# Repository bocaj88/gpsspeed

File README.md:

# GPSSpeed: a GPS replacement for the PerfectPass paddlewheel

**A small board that reads GPS speed and feeds it to PerfectPass as if it were the paddlewheel.**
Built for, and being tested on, our **2008 MasterCraft X2**. Everything is open: schematic, PCB,
firmware, and the notes on what didn't work along the way.

## The problem

**The paddlewheel speed sensor on our X2 went bad, and replacement sensors aren't sold anymore.**
Without it, PerfectPass has no speed to hold, so the speed control on the boat was dead.

PerfectPass holds a tow boat at a set speed by reading the boat's **paddlewheel speed sensor**: a
small wheel under the hull that spins in the water and sends one pulse per fraction of a turn.
On our X2 that sensor is part of an Airmar DST800-style triducer (speed, depth, temperature). It
sends about 20,000 pulses per nautical mile, and PerfectPass turns the pulse rate into speed.

Paddlewheels are the weak link:

- **They foul.** Weed, a fishing line, or a little growth, and the wheel drags or stops. PerfectPass
  then sees the wrong speed (or none) and drives the throttle accordingly.
- **You can't buy a replacement.** The DST800 is now an Airmar *legacy* product. Ours failed, and
  there was nothing to swap in.
- **They're never quite right.** Paddlewheel speed depends on the wheel, the hull, and how clean it
  is, so the dash and the real speed drift apart.

GPS speed doesn't have any of these problems. So the idea is simple: **read speed from GPS, and
generate the same pulse train the paddlewheel would**, on the same wire. PerfectPass doesn't know
the difference, and nothing else on the boat changes.

## How it works

```
 GPS antenna ──► ATGM336H GPS ──► ESP32-C3 ──► protected low-side switch ──► SIGNAL ──► PerfectPass
                 (10 Hz speed)    (pulse rate =      (open-drain, like the
                                   MPH × 4.42 Hz)     paddlewheel's own output)
 Boat 12 V ──► protection + buck ──► 3.3 V
```

- **Output:** a 50 % square wave whose frequency is proportional to speed: **4.42 Hz per MPH** by
  default (about 22 Hz at 5 MPH, 133 Hz at 30 MPH), calibrated from the phone app. It's generated by
  the ESP32's LEDC hardware timer from the 40 MHz crystal, so it's exact (worst-case 0.02 % error)
  and nothing in software can stretch a pulse.
- **No GPS fix yet:** it holds a steady 5 MPH. It never sweeps, because PerfectPass chases a sweep.
- **Lag compensation:** a small predictor projects speed ~0.3 s ahead from GPS acceleration, so
  PerfectPass isn't correcting late and hunting.
- **Phone app, no app install:** for 2 minutes after power-up the board runs its own WiFi network
  (`GPSSpeed-XXXX`, open). Join it and the app pops up: live speed, satellites, a self-test that
  steps through set speeds, a dash calibration table, settings, and **firmware updates over WiFi**.
  Then the radio turns itself off for the rest of the day on the water. It's also at
  `http://gpsspeed.local` while connected.
- **Wiring:** three screw terminals: **+12 V, GND, SIGNAL**.

## Status (October 2026)

| | |
|---|---|
| Hardware | **Rev 1.3**, 5 boards assembled by JLCPCB. Three external EE review rounds (summarized in [docs/04-design-reviews.md](docs/04-design-reviews.md)). |
| Bench-tested | Power, USB, GPS (13–16 satellites, fix indoors), antenna power, battery sense, phone app, **OTA update from an iPhone**. See [docs/05-bring-up.md](docs/05-bring-up.md). |
| Not yet tested | 12 V boat power, the output against a real PerfectPass input, on-water calibration. |
| Firmware | 4.0.8 (`firmware/gpsspeed_v4/bin/`) |

This is a prototype that hasn't run on the water yet. Read [the safety note](#safety) before
connecting it to a boat.

## 4 spare boards

We built 5 and need 1. **The other 4 are available** to anyone who wants to try this on their own
PerfectPass boat. They're fully assembled and flashed: you add an antenna and three wires. Reply in
the forum thread or open an issue on this repo.

## What you need to install one

The board, a GPS antenna, and three wires to the boat. The full list, with where to get each
cable and adapter, is in **[docs/06-wiring-and-cables.md](docs/06-wiring-and-cables.md)**.

## Repo map

| Path | What's there |
|---|---|
| [docs/](docs/) | The research: problem, history, design, reviews, bring-up, wiring, costs |
| [pcb/](pcb/) | KiCad 10 project, generator scripts, JLCPCB order files, renders. Start with [pcb/README.md](pcb/README.md) |
| [firmware/gpsspeed_v4/](firmware/gpsspeed_v4/) | ESP32-C3 firmware (Arduino core 3.3), prebuilt `.bin` images |
| [firmware/test/](firmware/test/) | Host-side tests of the pulse-generation and calibration math |
| [legacy/arduino-uno/](legacy/arduino-uno/) | The earlier Arduino Uno + perfboard builds (v1–v3) |
| [docs/forum-post.md](docs/forum-post.md) | The short version, for forums |

## Safety

This board changes what your speed control believes the boat is doing, and PerfectPass controls the
throttle. Test it at idle and low speed first. Keep a hand on the throttle, and know how to
disengage PerfectPass. Compare the dash against a phone GPS app before trusting it with a rider
behind the boat. Use it at your own risk; see the license.

## License

MIT (see [LICENSE](LICENSE)) for the firmware, scripts, docs and hardware design files.

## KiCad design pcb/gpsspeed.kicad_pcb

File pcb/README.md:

# GPSSpeed v4 — ESP32-C3 board

GPS → paddlewheel pulse emulator for PerfectPass, rebuilt as a JLCPCB-assembled
board. Replaces the Uno + perfboard hat.

| | |
|---|---|
| Size | 72 × 46 mm, 2 layers, 1.6 mm, 4× M3 holes |
| Power | **12/24 V DC nominal, 32 V continuous max.** 60 V polyfuse → 1.5 kW bidirectional TVS (±58 V clamp) → 100 V reverse-polarity Schottky → 22 µF/100 V bulk + 4 × 2.2 µF/100 V → LMR38010 buck (80 V operating, 85 V abs max). USB-C on the bench. |
| Brain | ESP32-C3-MINI-1-H4 (WiFi boot window, OTA updates; 105 °C part) |
| GPS | ATGM336H-5N31 (GPS+BeiDou, 10 Hz), u.FL for the existing active antenna |
| Output | ZXMS6004FF self-protected low-side switch (60 V, current limit, thermal shutdown, active clamp) behind a series Schottky (swapped +12 V/GND can't back-drive the dash), 33 V TVS on the drain; survives SIGNAL wired to +12 V; optional pull-up to the input rail via JP1 (ships **open**) |
| Connector | J1 screw terminal: **1 = +12 V, 2 = GND, 3 = SIGNAL** (wires enter from the board edge) |
| LEDs | PWR (red), GPS (green), WIFI (green) |

## Rev 1.3 — third EE review (independent)

| Review item | Change |
|---|---|
| Stop-ship: SIGNAL wired to +12 V shorts the supply through D5 and a bare 2N7002K the first time Q1 turns on | Q1 → **ZXMS6004FF** IntelliFET: current limit 0.7–1.7 A, thermal shutdown with auto-restart, short-circuit protected to V<sub>DS</sub> 36 V. Specified for 3.3 V logic (V<sub>IH</sub> 3 V, 0.6 Ω max at 3 V) |
| D4 (53 V max clamp) vs Q1 (60 V) margin thin | Q1's own active clamp is 60–70 V / 90 mJ, so a spike past D4 is absorbed by design instead of avalanching a bare MOSFET |
| (follows from the above) | SIGNAL_OUT / SIGNAL_DRAIN routed at **0.5 mm** for the 1.7 A fault current |

Bench items from that review (not schematic errors): output-low level with D5 in series against the real
PerfectPass input; USB-only startup at ~4.6 V into the buck. JP1 stays open on 24 V boats.
Q1 switching: ~15 µs on / ~60 µs off. Constant edge delays leave the output frequency unchanged; duty
shifts by ~1 % at 60 MPH.

## Rev 1.2 — second EE review (reviewed the native KiCad files)

| Review item | Change |
|---|---|
| C16 only 63 V against a 58 V clamp | **22 µF / 100 V**, same series and 6.3 × 7.7 can (RV100V22M6X8) |
| Battery-sense pin reaches 3.6 V at the clamp | R1 150k → **220k** (×23): 32 V reads 1.4 V, the 58 V clamp 2.5 V. Firmware **4.0.2** |
| Input ceramics borderline after DC-bias derating | **4th 2.2 µF / 100 V** (C17) |
| 24 V pull-up would forward-bias D5 and make D4 clamp continuously | Q1 → **2N7002K 60 V**, D4 → **SMF33A** (33 V standoff, 53 V clamp < 60 V) |
| Buck exposed pad: one full paste opening, no thermal path | Paste split into **4 windows (60 %)**; **2 tented GND vias** just past the GND-pin end of the pad; pad tied solid into the pour |
| (found while re-checking) | Two u.FL stitching vias overlapped fanout vias (drill-to-drill). Fanout now avoids existing vias, and drill spacing fails the build |

Not changed: L1 stays where it is (SW node ~8.7 mm total; moving it means relocating D2 in the
packed input corner — the reviewer rated it optional for prototypes). D2 stays an SS310: it has
to block up to ~53 V when USB and boat power are both connected, and USB power is bench-only.

## Rev 1.1 — changes from the external EE review

| Review item | Change |
|---|---|
| "12–24 V" label wrong (old TVS conducted ~20 V) | Input re-rated; silk now reads **12/24V DC 32V MAX** |
| TVS + PTC too close to the AP63203's 35 V abs max | Buck → **LMR38010** (80 V / 85 V abs), TVS → **SMCJ36CA** 1.5 kW bidirectional, PTC → 60 V, D1/D2 → **SS310** 100 V, input ceramics → 100 V, + **47 µF/63 V** bulk |
| L2's 1.2 GHz SRF below GPS L1 | L2 → **Murata LQW18AN27NG** wirewound, SRF 3.7 GHz |
| SIGNAL back-drive on reverse wiring | **D5 SS310 in series** at J1 pin 3 (chosen over a resistor so a stiff head-unit pull-up can't break the low level; adds ~0.3 V) |
| Open via-in-pad under the ESP32 | Removed; also stripped 4 open vias JLC's footprint put in the buck's exposed pad |
| Buck loop / u.FL grounding | Hand-routed C3–VIN–GND loop (~2 mm), SW straight into L1, FB on the quiet side; 8 stitching vias around the u.FL |

Not changed (reviewed and accepted): USB diode-OR (verify startup during WiFi TX on the bench),
reboot on very deep crank dips (firmware ignores brownouts for rollback), SMF15A on the drain
(24.4 V clamp < Q1's 30 V).

**Potting:** keep resin off the ESP32 antenna end (top edge) — resin detunes the PCB antenna.
Leave an air pocket there, or pot only the lower two-thirds of the board.

## What fixes the old problems

- **21 MPH cliff:** gone. The square wave comes from the LEDC hardware peripheral off
  the 40 MHz crystal; no software can stretch it. Measured on the real firmware code:
  worst frequency error **0.02 %** across 1–60 MPH (the Uno drifted up to 2.5 % fast
  at 30 MPH from its 128 µs rounding).
- **One serial port:** the GPS has its own hardware UART; USB-C serial is always free.
- **Tuning at the dock with a laptop:** everything is edited from your phone.

## Files

```
pcb/
  gpsspeed.kicad_pro / .kicad_sch / .kicad_pcb   open in KiCad 10
  gpsspeed.kicad_dru      two scoped DRC exceptions (explained inside)
  lib/                    exact JLC footprints/symbols/3D (easyeda2kicad)
  gen/                    the generators -- design.py is the netlist source of truth
  out/jlcpcb/             gerbers.zip, bom_jlcpcb.csv, cpl_jlcpcb.csv   <- upload these
  out/                    schematic PDF, assembly PDF, STEP, renders
firmware/gpsspeed_v4/     ESP32-C3 firmware; bin/ has prebuilt images
firmware/test/            host-side tests of the pulse + calibration code
```

## Ordering at JLCPCB

1. **PCB:** upload `out/jlcpcb/gerbers.zip`. Defaults are right: 2 layers, 1.6 mm,
   HASL lead-free, green. Qty 5 (the minimum).
2. **PCB Assembly:** on, *Standard*, *Top side*, qty **5**. (Economic won't take
   the ESP32 module -- JLC flags every ESP32-C3-MINI-1 "Standard PCBA only".)
3. Upload `bom_jlcpcb.csv` and `cpl_jlcpcb.csv`.
4. In the **parts review**, every line should match an LCSC number. J1 (screw
   terminal) is through-hole; if Economic won't place it, untick it and solder its
   3 pins by hand.
5. In the **placement preview**, check polarity/pin-1 on: D1–D5, C16 (+), LED1–3, U1–U4, Q1,
   J2, J3. Footprints came from JLC's own library, so rotations should already
   match, but this is the one step a human should eyeball.

Rev 1.1 quote (2026-09-26), for reference: 5 assembled boards $162.84, + UPS ~$37 + US
customs duty ~$61 (JLC collects it up front with DDP shipping) − $10 coupon ≈ $251.

## Bring-up

1. **Before power:** meter +12 V to GND on J1 — must not beep.
2. **USB-C only first.** PWR LED on, TP2 = 3.3 V.
3. Flash once over USB-C:
   ```
   esptool.py --chip esp32c3 write_flash 0x0 firmware/gpsspeed_v4/bin/gpsspeed_v4-4.0.8-usb-full.bin
   ```
   (or `arduino-cli upload` — build command is in `gpsspeed_v4.ino`). If it won't
   connect, hold **BOOT**, tap **RST**, release BOOT.
4. Serial monitor at 115200: expect `chars:` climbing and `ant:OK` once the antenna
   is on. `ant:OPEN` = antenna not connected / passive; `ant:SHORT` = cable fault.
5. Plug in the antenna, go outside, wait for the GPS LED to go solid.
6. **Then** wire the boat: +12 V, GND, SIGNAL to the paddlewheel signal line.

## Using it on the boat

- Power on → join WiFi **`GPSSpeed-XXXX`** (open, no password; XXXX is fixed per board) → the page pops up, tap **Done** → later just open **http://gpsspeed.local**
  (Safari; a captive-portal sheet may open on its own).
- The access point lives **2 minutes** after power-on, extends while your phone is
  connected, then turns the radio off. To get back in: cycle power.
- **Calibrate once:** tap *Self-test*, and at each step type what the dash shows into
  *Dash shows* → *Save point*. One pass gets the dash within ~0.01 MPH at the
  calibrated speeds (tested against a simulated nonlinear dash).
- While GPS is searching the output holds a steady **5 MPH** (never sweeps).
- **Firmware updates:** *Firmware → Upload* the `-ota.bin`. A bad build that
  crash-loops rolls back to the previous one automatically; brownouts from engine
  cranking do not count as crashes.

## Things I could not verify without hardware

- **CASIC config commands** (`$PCAS01/02/03`) follow ZhongKe's documented format. If
  the module ignores one, the firmware still works at its defaults (9600 baud, 1 Hz)
  — the web UI shows the actual baud/rate it achieved.
- **Default Hz/MPH is 4.42**, the Uno's *effective* constant at 15–26 MPH. Expect to
  run the self-test once.
- **Active antenna assumed** (GT-U7 kits ship with one). For a passive antenna,
  remove L2.
- **Wiring polarity:** the board survives +12 V/GND swapped (D5 keeps the swap from
  back-driving the dash input) and SIGNAL wired to +12 V (Q1 current-limits and thermal-cycles).
  Still meter it before powering.
- **JP1 on 24 V boats:** leave it open. Bridged at 28.8 V, R15 (0603) runs near its 0.1 W
  rating; the dash's own pull-up is the normal case anyway.

## Regenerating

```
cd pcb/gen
~/Applications/KiCad/KiCad.app/Contents/Frameworks/Python.framework/Versions/3.9/bin/python3 gen_sch.py
~/Applications/KiCad/KiCad.app/Contents/Frameworks/Python.framework/Versions/3.9/bin/python3 build.py   # place, route, pour, DRC
python3 gen_outputs.py                                                                                  # JLC files
```
`build.py` needs Freerouting (`~/Applications/freerouting`) and Java ≥ 25
(`brew install openjdk`). Edit `design.py` for circuit changes, `gen_pcb.py` for
placement.

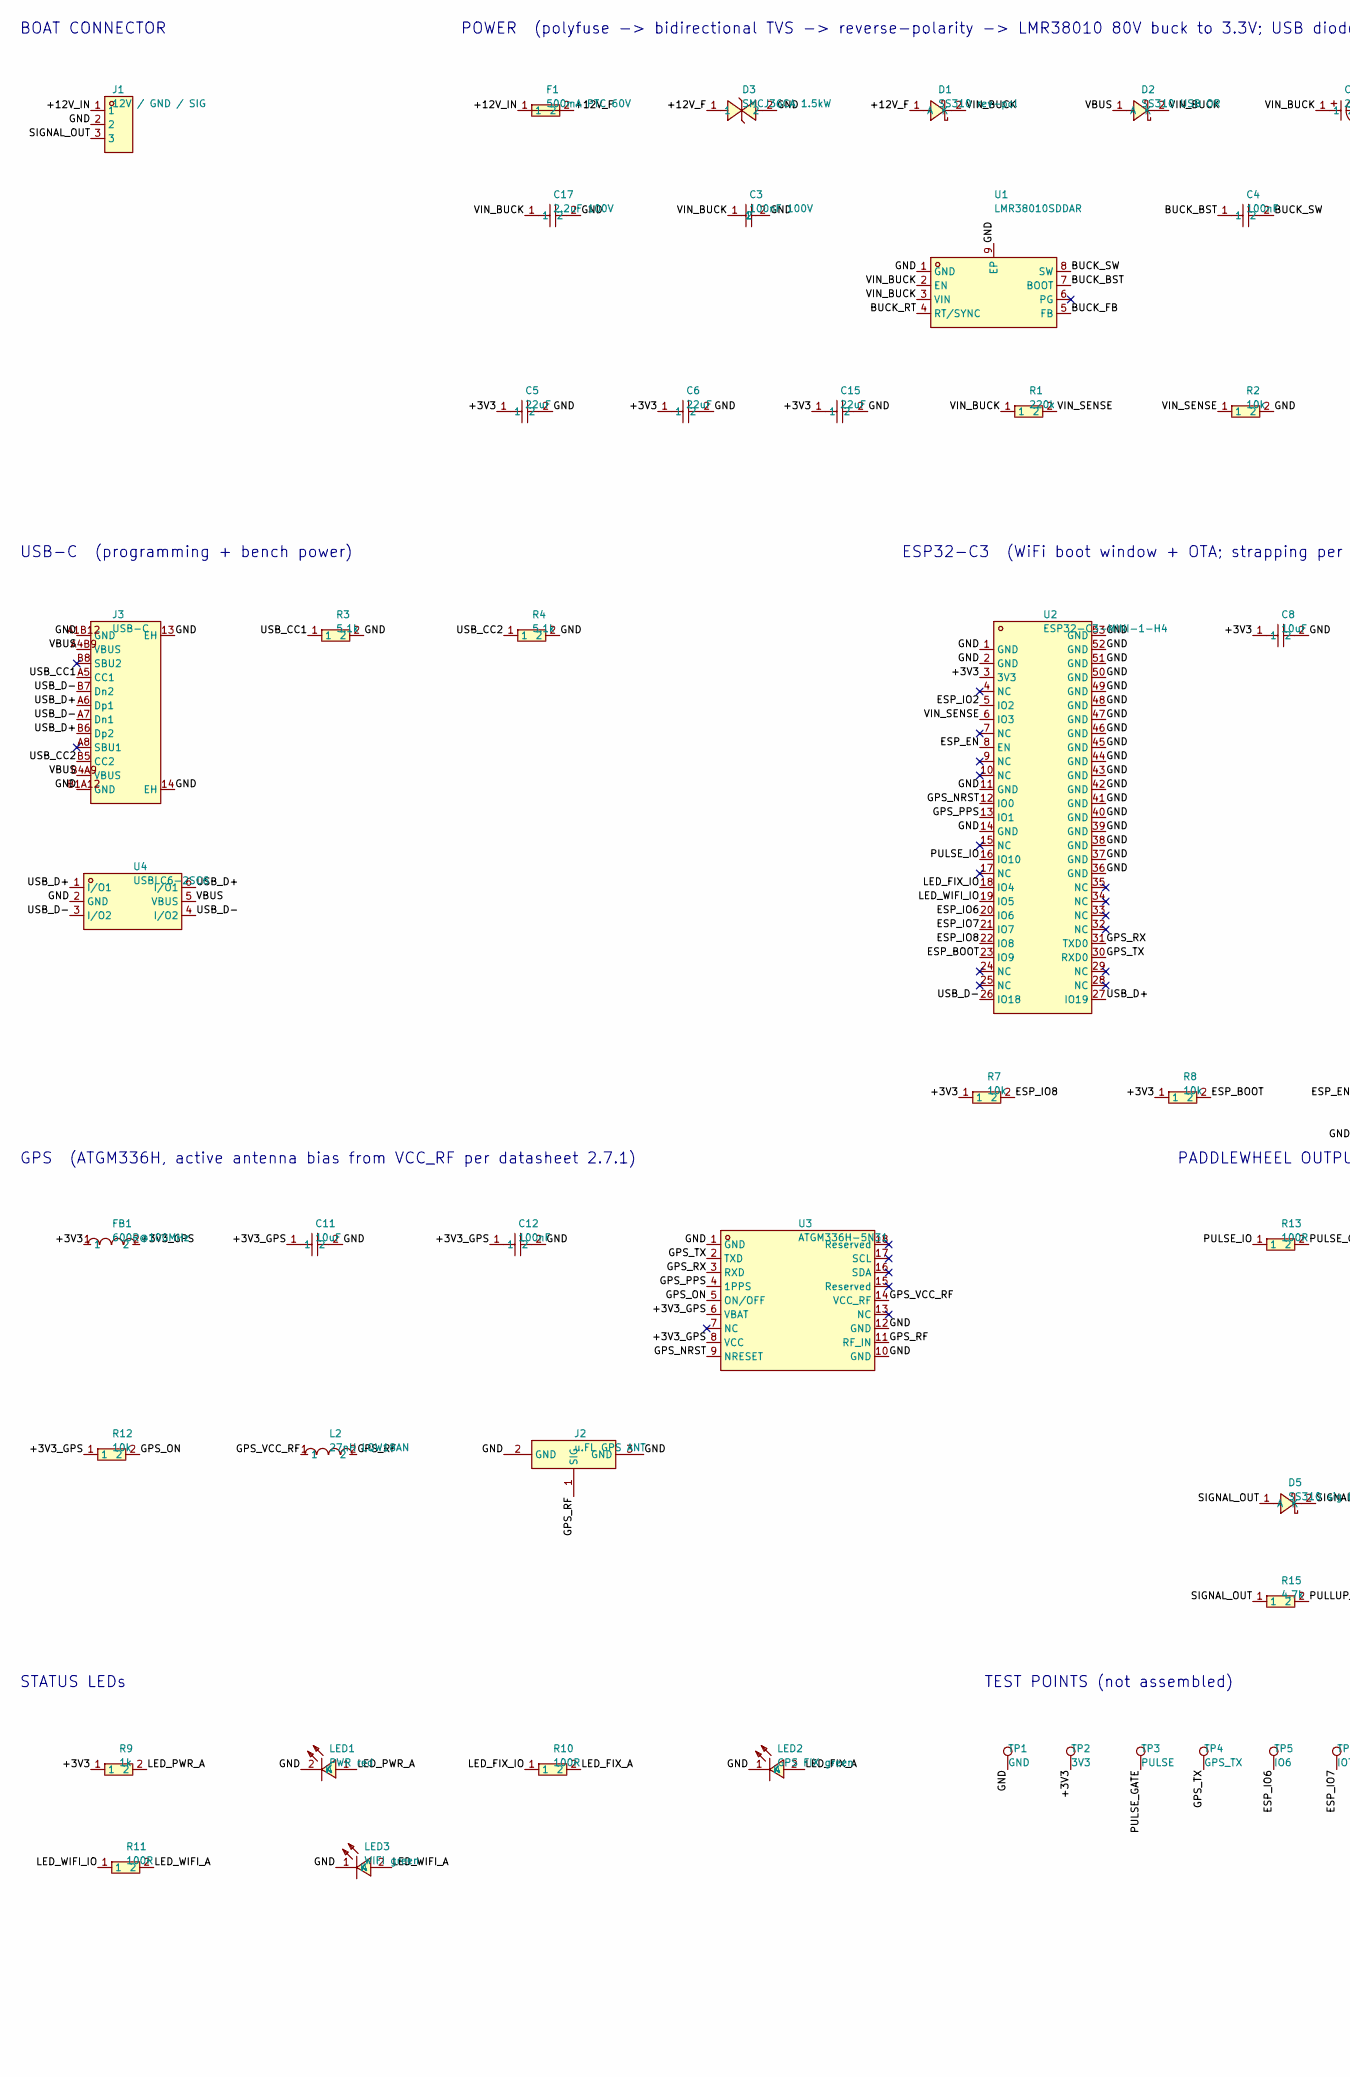
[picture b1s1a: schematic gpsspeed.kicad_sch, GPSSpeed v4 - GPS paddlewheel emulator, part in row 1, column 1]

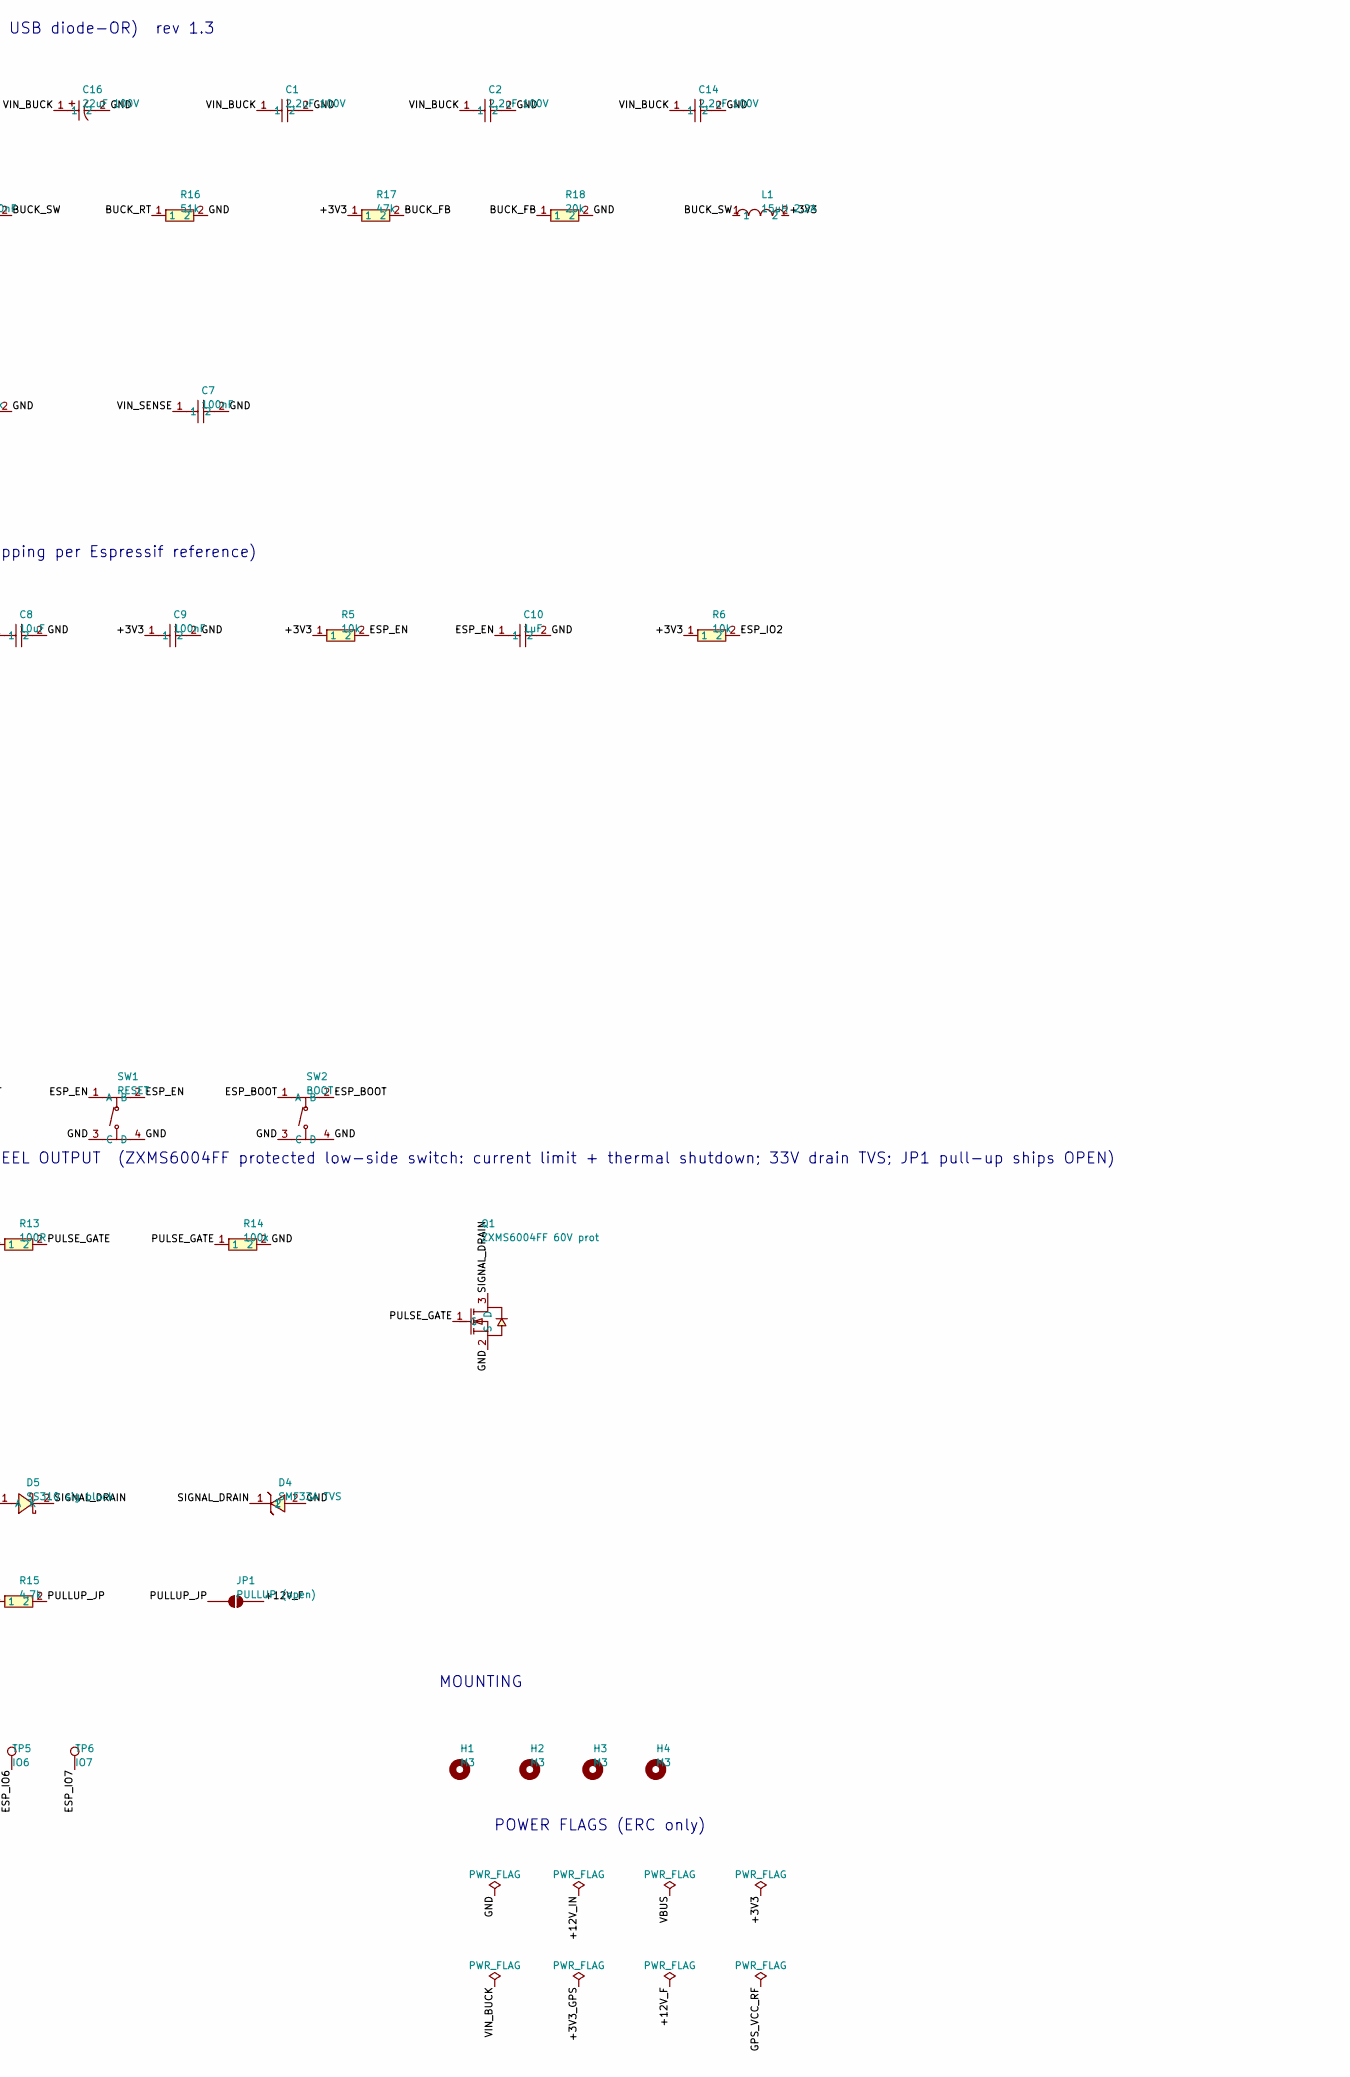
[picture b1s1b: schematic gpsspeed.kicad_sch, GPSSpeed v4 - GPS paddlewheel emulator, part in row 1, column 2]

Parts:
C1, C2, C14, C17: 2.2uF 100V; C1206; LCSC C170101
C3: 100nF 100V; C0805; LCSC C28233
C4, C7, C9, C12: 100nF; C0603; LCSC C14663
C5, C6, C15: 22uF; C0805; LCSC C45783
C8, C11: 10uF; C0805; LCSC C15850
C10: 1uF; C0603; LCSC C15849
C16: 22uF 100V; CAP-SMD_BD6.3-L6.6-W6.6-LS7.4-FD; LCSC C48971012
D1: SS310 rev-pol; SMA_L4.3-W2.6-LS5.0-FD; LCSC C7420364
D2: SS310 USB OR; SMA_L4.3-W2.6-LS5.0-FD; LCSC C7420364
D3: SMCJ36CA 1.5kW; SMC_L6.9-W5.9-LS7.9-BI; LCSC C19077609
D4: SMF33A TVS; SOD-123FL_L2.7-W1.8-LS3.8-RD; LCSC C726914
D5: SS310 sig block; SMA_L4.3-W2.6-LS5.0-FD; LCSC C7420364
F1: 500mA PTC 60V; F1812; LCSC C19078719
FB1: 600R@100MHz; L0603; LCSC C1002
H1, H2, H3, H4: M3; MountingHole_3.2mm_M3
J1: 12V / GND / SIG; CONN-TH_3P-P5.00_KF301-5.0-3P; LCSC C474882
J2: u.FL GPS ANT; RF-SMD_FRF05002-JSS103M; LCSC C88374
J3: USB-C; USB-C-SMD_TYPE-C-16PIN-2MD-073; LCSC C2765186
JP1: PULLUP (open); SolderJumper-2_P1.3mm_Open_RoundedPad1.0x1.5mm
L1: 15uH 2.2A; IND-SMD_L5.0-W5.0; LCSC C167969
L2: 27nH LQW18AN; IND-SMD_L1.6-W0.8-1; LCSC C148128
LED1: PWR red; LED-SMD_L1.6-W0.8-R-RD; LCSC C2286
LED2: GPS FIX green; LED0603-RD; LCSC C12624
LED3: WIFI green; LED0603-RD; LCSC C12624
Q1: ZXMS6004FF 60V prot; SOT-23-3_L2.9-W1.6-P1.90-LS2.8-BR; LCSC C95063
R1: 220k; R0603; LCSC C22961
R2, R5, R6, R7, R8, R12: 10k; R0603; LCSC C25804
R3, R4: 5.1k; R0603; LCSC C23186
R9: 1k; R0603; LCSC C21190
R10, R11, R13: 100R; R0603; LCSC C22775
R14: 100k; R0603; LCSC C25803
R15: 4.7k; R0603; LCSC C23162
R16: 51k; R0603; LCSC C23196
R17: 47k; R0603; LCSC C25819
R18: 20k; R0603; LCSC C4184
SW1: RESET; SW-SMD_4P-L5.1-W5.1-P3.70-LS6.5-TL_H1.5; LCSC C318884
SW2: BOOT; SW-SMD_4P-L5.1-W5.1-P3.70-LS6.5-TL_H1.5; LCSC C318884
TP1: GND; TestPoint_Pad_D1.5mm
TP2: 3V3; TestPoint_Pad_D1.5mm
TP3: PULSE; TestPoint_Pad_D1.5mm
TP4: GPS_TX; TestPoint_Pad_D1.5mm
TP5: IO6; TestPoint_Pad_D1.5mm
TP6: IO7; TestPoint_Pad_D1.5mm
U1: LMR38010SDDAR; SOIC-8_L4.9-W3.9-P1.27-LS6.0-BL-EP-1; LCSC C5219310
U2: ESP32-C3-MINI-1-H4; WIFIM-SMD_ESP32-C3-MINI-1; LCSC C2934569
U3: ATGM336H-5N31; GPSM-SMD_ATGM336H-TR; LCSC C90770
U4: USBLC6-2SC6; SOT-23-6_L2.9-W1.6-P0.95-LS2.8-BL; LCSC C2687116

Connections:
+3V3: C5.1, C6.1, C8.1, C9.1, C15.1, FB1.1, L1.2, R5.1, R6.1, R7.1, R8.1, R9.1, R17.1, TP2.1, U2.3 (3V3)
+3V3_GPS: C11.1, C12.1, FB1.2, R12.1, U3.6 (VBAT), U3.8 (VCC)
+12V_F: D1.1 (A), D3.1, F1.2, JP1.2 (B)
+12V_IN: F1.1, J1.1
BUCK_BST: C4.1, U1.7 (BOOT)
BUCK_FB: R17.2, R18.1, U1.5 (FB)
BUCK_RT: R16.1, U1.4 (RT/SYNC)
BUCK_SW: C4.2, L1.1, U1.8 (SW)
ESP_BOOT: R8.2, SW2.1 (A), SW2.2 (B), U2.23 (IO9)
ESP_EN: C10.1, R5.2, SW1.1 (A), SW1.2 (B), U2.8 (EN)
ESP_IO2: R6.2, U2.5 (IO2)
ESP_IO6: TP5.1, U2.20 (IO6)
ESP_IO7: TP6.1, U2.21 (IO7)
ESP_IO8: R7.2, U2.22 (IO8)
GND: C1.2, C2.2, C3.2, C5.2, C6.2, C7.2, C8.2, C9.2, C10.2, C11.2, C12.2, C14.2, C15.2, C16.2, C17.2, D3.2, D4.2, J1.2, J2.2 (GND), J2.3 (GND), J3.13 (EH), J3.14 (EH), J3.A1B12 (GND), J3.B1A12 (GND), LED1.2 (K), LED2.1 (K), LED3.1 (K), Q1.2 (S), R2.2, R3.2, R4.2, R14.2, R16.2, R18.2, SW1.3 (C), SW1.4 (D), SW2.3 (C), SW2.4 (D), TP1.1, U1.1 (GND), U1.9 (EP), U2.1 (GND), U2.2 (GND), U2.11 (GND), U2.14 (GND), U2.36 (GND), U2.37 (GND), U2.38 (GND), U2.39 (GND), U2.40 (GND), U2.41 (GND), U2.42 (GND), U2.43 (GND), U2.44 (GND), U2.45 (GND), U2.46 (GND), U2.47 (GND), U2.48 (GND), U2.49 (GND), U2.50 (GND), U2.51 (GND), U2.52 (GND), U2.53 (GND), U3.1 (GND), U3.10 (GND), U3.12 (GND), U4.2 (GND)
GPS_NRST: U2.12 (IO0), U3.9 (NRESET)
GPS_ON: R12.2, U3.5 (ON/OFF)
GPS_PPS: U2.13 (IO1), U3.4 (1PPS)
GPS_RF: J2.1 (SIG), L2.2, U3.11 (RF_IN)
GPS_RX: U2.31 (TXD0), U3.3 (RXD)
GPS_TX: TP4.1, U2.30 (RXD0), U3.2 (TXD)
GPS_VCC_RF: L2.1, U3.14 (VCC_RF)
LED_FIX_A: LED2.2 (A), R10.2
LED_FIX_IO: R10.1, U2.18 (IO4)
LED_PWR_A: LED1.1 (A), R9.2
LED_WIFI_A: LED3.2 (A), R11.2
LED_WIFI_IO: R11.1, U2.19 (IO5)
PULLUP_JP: JP1.1 (A), R15.2
PULSE_GATE: Q1.1 (G), R13.2, R14.1, TP3.1
PULSE_IO: R13.1, U2.16 (IO10)
SIGNAL_DRAIN: D4.1, D5.2 (K), Q1.3 (D)
SIGNAL_OUT: D5.1 (A), J1.3, R15.1
USB_CC1: J3.A5 (CC1), R3.1
USB_CC2: J3.B5 (CC2), R4.1
USB_D+: J3.A6 (Dp1), J3.B6 (Dp2), U2.27 (IO19), U4.1 (I/O1), U4.6 (I/O1)
USB_D-: J3.A7 (Dn1), J3.B7 (Dn2), U2.26 (IO18), U4.3 (I/O2), U4.4 (I/O2)
VBUS: D2.1 (A), J3.A4B9 (VBUS), J3.B4A9 (VBUS), U4.5 (VBUS)
VIN_BUCK: C1.1, C2.1, C3.1, C14.1, C16.1, C17.1, D1.2 (K), D2.2 (K), R1.1, U1.2 (EN), U1.3 (VIN)
VIN_SENSE: C7.1, R1.2, R2.1, U2.6 (IO3)

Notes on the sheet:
BOAT CONNECTOR
POWER (polyfuse -> bidirectional TVS -> reverse-polarity -> LMR38010 80V buck to 3.3V; USB diode-OR) rev 1.3
USB-C (programming + bench power)
ESP32-C3 (WiFi boot window + OTA; strapping per Espressif reference)
GPS (ATGM336H, active antenna bias from VCC_RF per datasheet 2.7.1)
PADDLEWHEEL OUTPUT (ZXMS6004FF protected low-side switch: current limit + thermal shutdown; 33V drain TVS; JP1 pull-up ships OPEN)
STATUS LEDs
TEST POINTS (not assembled)
MOUNTING
POWER FLAGS (ERC only)

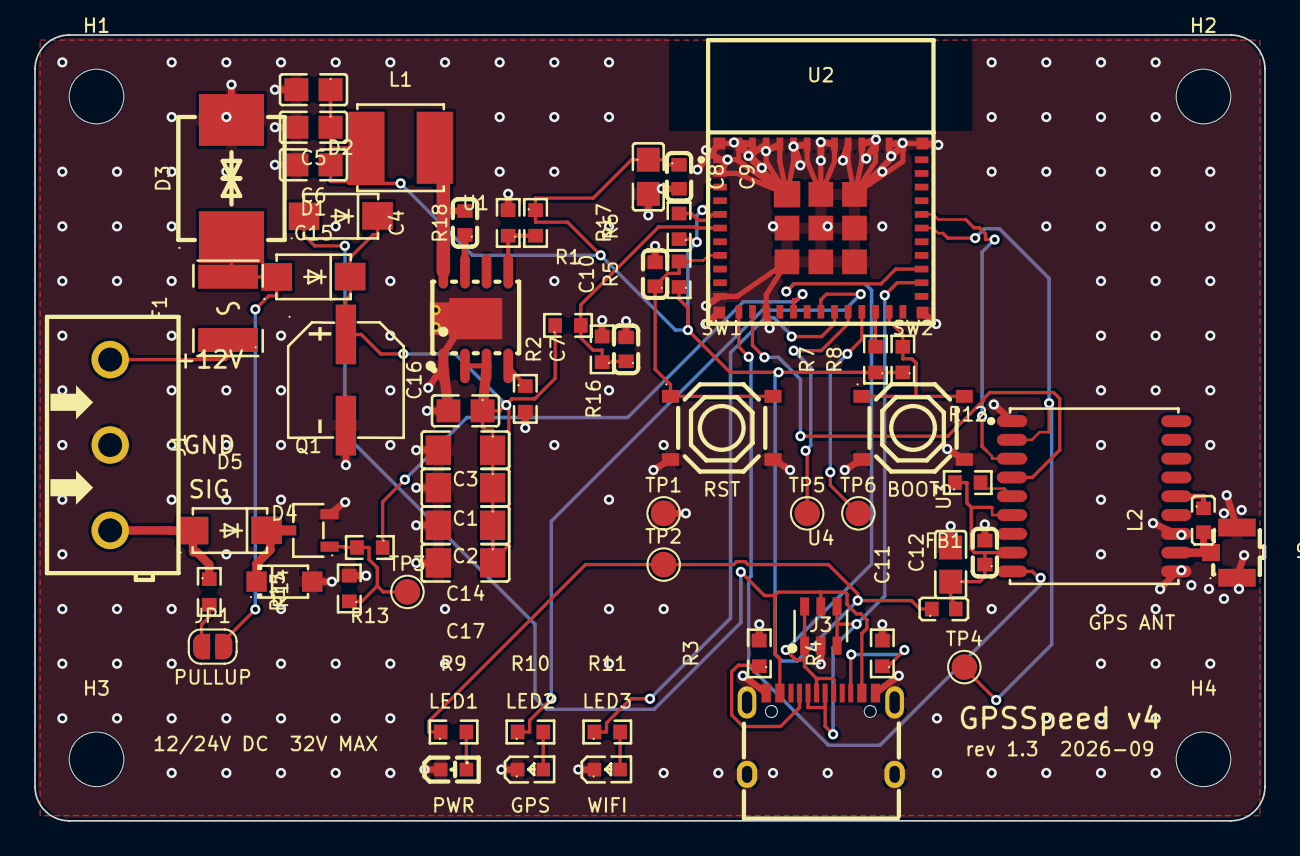
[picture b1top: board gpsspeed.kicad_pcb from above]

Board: 2 copper layers, 72.0 x 46.0 mm, 67 parts (0 on the bottom side), 39 nets.

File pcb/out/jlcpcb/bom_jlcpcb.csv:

Comment,Designator,Footprint,LCSC Part #
12V / GND / SIG,J1,CONN-TH_3P-P5.00_KF301-5.0-3P,C474882
500mA PTC 60V,F1,F1812,C19078719
SMCJ36CA 1.5kW,D3,SMC_L6.9-W5.9-LS7.9-BI,C19077609
SS310 rev-pol,"D1,D2,D5",SMA_L4.3-W2.6-LS5.0-FD,C7420364
22uF 100V,C16,CAP-SMD_BD6.3-L6.6-W6.6-LS7.4-FD,C48971012
2.2uF 100V,"C1,C2,C14,C17",C1206,C170101
100nF 100V,C3,C0805,C28233
LMR38010SDDAR,U1,SOIC-8_L4.9-W3.9-P1.27-LS6.0-BL-EP-1,C5219310
100nF,"C4,C7,C9,C12",C0603,C14663
51k,R16,R0603,C23196
47k,R17,R0603,C25819
20k,R18,R0603,C4184
15uH 2.2A,L1,IND-SMD_L5.0-W5.0,C167969
22uF,"C5,C6,C15",C0805,C45783
220k,R1,R0603,C22961
10k,"R2,R5,R6,R7,R8,R12",R0603,C25804
USB-C,J3,USB-C-SMD_TYPE-C-16PIN-2MD-073,C2765186
5.1k,"R3,R4",R0603,C23186
USBLC6-2SC6,U4,SOT-23-6_L2.9-W1.6-P0.95-LS2.8-BL,C2687116
ESP32-C3-MINI-1-H4,U2,WIFIM-SMD_ESP32-C3-MINI-1,C2934569
10uF,"C8,C11",C0805,C15850
1uF,C10,C0603,C15849
RESET,"SW1,SW2",SW-SMD_4P-L5.1-W5.1-P3.70-LS6.5-TL_H1.5,C318884
1k,R9,R0603,C21190
PWR red,LED1,LED-SMD_L1.6-W0.8-R-RD,C2286
100R,"R10,R11,R13",R0603,C22775
GPS FIX green,"LED2,LED3",LED0603-RD,C12624
600R@100MHz,FB1,L0603,C1002
ATGM336H-5N31,U3,GPSM-SMD_ATGM336H-TR,C90770
27nH LQW18AN,L2,IND-SMD_L1.6-W0.8-1,C148128
u.FL GPS ANT,J2,RF-SMD_FRF05002-JSS103M,C88374
100k,R14,R0603,C25803
ZXMS6004FF 60V prot,Q1,SOT-23-3_L2.9-W1.6-P1.90-LS2.8-BR,C95063
SMF33A TVS,D4,SOD-123FL_L2.7-W1.8-LS3.8-RD,C726914
4.7k,R15,R0603,C23162

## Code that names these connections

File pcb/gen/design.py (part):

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SW       = "BUCK_SW"
BST      = "BUCK_BST"
EN       = "ESP_EN"
BOOT     = "ESP_BOOT"    # GPIO9
STRAP2   = "ESP_IO2"
STRAP8   = "ESP_IO8"
USB_DP   = "USB_D+"
USB_DN   = "USB_D-"
CC1      = "USB_CC1"
CC2      = "USB_CC2"
GPS_TX   = "GPS_TX"      # GPS TXD -> ESP RX (GPIO20 / RXD0)
GPS_RX   = "GPS_RX"      # ESP TX (GPIO21 / TXD0) -> GPS RXD
GPS_PPS  = "GPS_PPS"
GPS_NRST = "GPS_NRST"
GPS_ONOFF= "GPS_ON"
RF_ANT   = "GPS_RF"
VCC_RF   = "GPS_VCC_RF"
VSENSE   = "VIN_SENSE"
PULSE    = "PULSE_IO"    # ESP GPIO10 (LEDC hardware PWM)
GATE     = "PULSE_GATE"
SIG_OUT  = "SIGNAL_OUT"  # J1 pin 3 -> PerfectPass paddlewheel input
PU_EN    = "PULLUP_JP"
LED_FIX  = "LED_FIX_IO"
LED_WIFI = "LED_WIFI_IO"
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    # still visible off a 3.3V GPIO.
    R("R9",  "0603WAF1001T5E", "C21190", "1k", V3V3, LED_PWR_A, "led"),
    dict(ref="LED1", sym="KT-0603R", lcsc="C2286", value="PWR red",
         pins={"A": LED_PWR_A, "K": GND}, grp="led"),
    R("R10", "0603WAF1000T5E", "C22775", "100R", LED_FIX, LED_FIX_A, "led"),
    dict(ref="LED2", sym="0603Green509-620mcd", lcsc="C12624", value="GPS FIX green",
         pins={"A": LED_FIX_A, "K": GND}, grp="led"),
    R("R11", "0603WAF1000T5E", "C22775", "100R", LED_WIFI, LED_WIFI_A, "led"),
    dict(ref="LED3", sym="0603Green509-620mcd", lcsc="C12624", value="WIFI green",
         pins={"A": LED_WIFI_A, "K": GND}, grp="led"),

    # ---------------- GPS (ATGM336H datasheet 2.7.1 active antenna) ------
    R("FB1", "GZ1608D601TF", "C1002", "600R@100MHz", V3V3, V3V3_GPS, "gps"),
    R("C11", "CL21A106KAYNNNE", "C15850", "10uF", V3V3_GPS, GND, "gps"),
    R("C12", "CC0603KRX7R9BB104", "C14663", "100nF", V3V3_GPS, GND, "gps"),
    dict(ref="U3", sym="ATGM336H-5N31", lcsc="C90770", value="ATGM336H-5N31",
         pins={"GND": GND, "TXD": GPS_TX, "RXD": GPS_RX, "1PPS": GPS_PPS,
               "ON/OFF": GPS_ONOFF, "VBAT": V3V3_GPS, "VCC": V3V3_GPS,
               "NRESET": GPS_NRST, "RF_IN": RF_ANT, "VCC_RF": VCC_RF},
         grp="gps"),
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    dict(ref="TP3", sym="Connector:TestPoint", lcsc=None, value="PULSE",
         fp="TestPoint:TestPoint_Pad_D1.5mm", pins={"1": GATE}, grp="tp"),
    dict(ref="TP4", sym="Connector:TestPoint", lcsc=None, value="GPS_TX",
         fp="TestPoint:TestPoint_Pad_D1.5mm", pins={"1": GPS_TX}, grp="tp"),
    dict(ref="TP5", sym="Connector:TestPoint", lcsc=None, value="IO6",
         fp="TestPoint:TestPoint_Pad_D1.5mm", pins={"1": IO6}, grp="tp"),
    dict(ref="TP6", sym="Connector:TestPoint", lcsc=None, value="IO7",
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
